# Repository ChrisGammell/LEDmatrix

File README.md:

# LEDmatrix
Simple LED Matrix board

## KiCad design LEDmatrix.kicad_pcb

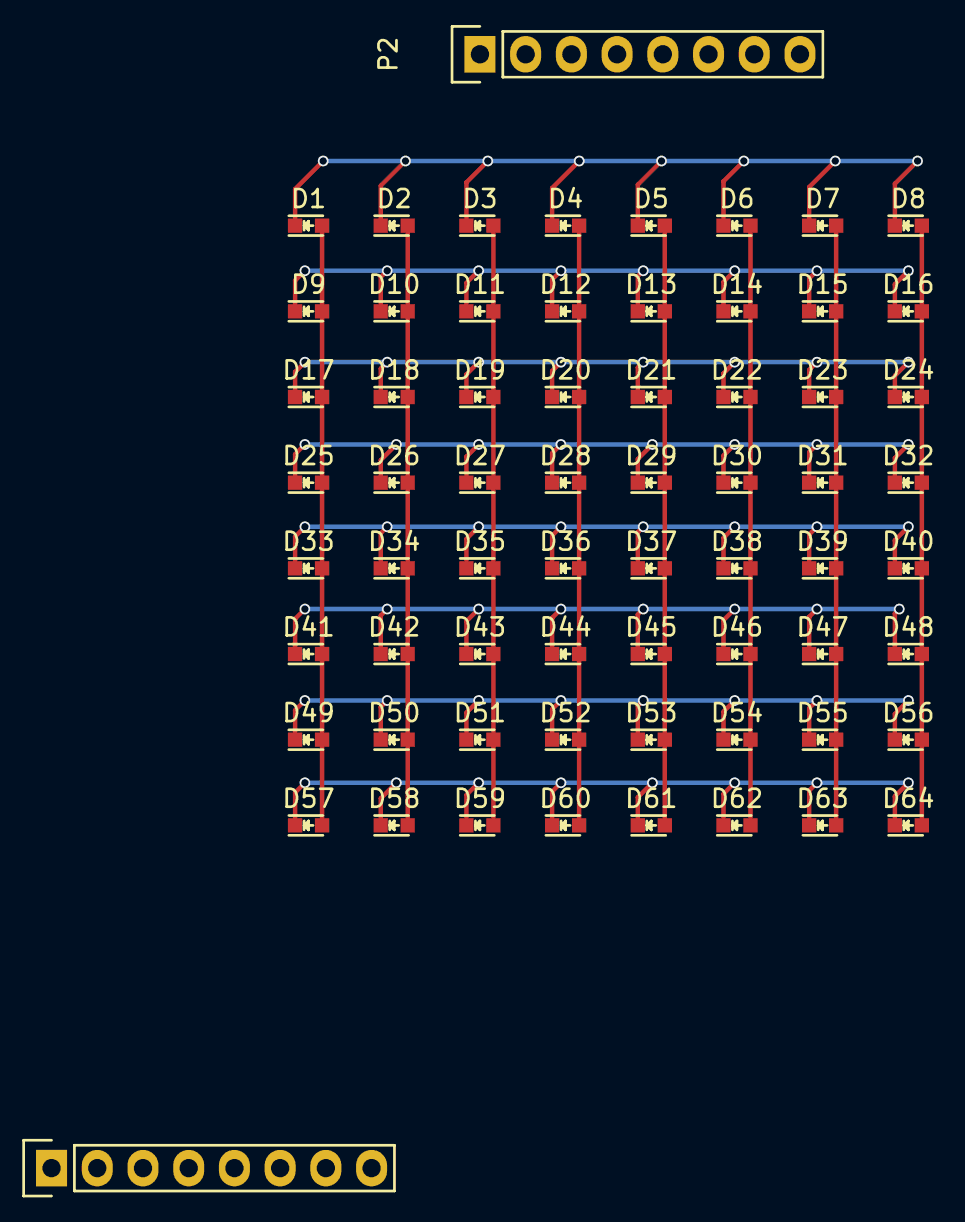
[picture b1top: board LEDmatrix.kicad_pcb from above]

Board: 2 copper layers, 66 parts (0 on the bottom side), 16 nets.

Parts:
D1, D2, D3, D4, D5, D6, D7, D8, D9, D10, D11, D12, D13, D14, D15, D16, D17, D18, D19, D20, D21, D22, D23, D24, D25, D26, D27, D28, D29, D30, D31, D32, D33, D34, D35, D36, D37, D38, D39, D40, D41, D42, D43, D44, D45, D46, D47, D48, D49, D50, D51, D52, D53, D54, D55, D56, D57, D58, D59, D60, D61, D62, D63, D64: LED; LED_0603
P1, P2: CONN_01X08; Pin_Header_Straight_1x08

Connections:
unnamed: D1.1, D2.1, D3.1, D4.1, D5.1, D6.1, D7.1, D8.1, P1.1
unnamed: D1.2, D9.2, D17.2, D25.2, D33.2, D41.2, D49.2, D57.2, P2.1
unnamed: D9.1, D10.1, D11.1, D12.1, D13.1, D14.1, D15.1, D16.1, P1.2
unnamed: D2.2, D10.2, D18.2, D26.2, D34.2, D42.2, D50.2, D58.2, P2.2
unnamed: D3.2, D11.2, D19.2, D27.2, D35.2, D43.2, D51.2, D59.2, P2.3
unnamed: D4.2, D12.2, D20.2, D28.2, D36.2, D44.2, D52.2, D60.2, P2.4
unnamed: D5.2, D13.2, D21.2, D29.2, D37.2, D45.2, D53.2, D61.2, P2.5
unnamed: D6.2, D14.2, D22.2, D30.2, D38.2, D46.2, D54.2, D62.2, P2.6
unnamed: D7.2, D15.2, D23.2, D31.2, D39.2, D47.2, D55.2, D63.2, P2.7
unnamed: D8.2, D16.2, D24.2, D32.2, D40.2, D48.2, D56.2, D64.2, P2.8
unnamed: D17.1, D18.1, D19.1, D20.1, D21.1, D22.1, D23.1, D24.1, P1.3
unnamed: D25.1, D26.1, D27.1, D28.1, D29.1, D30.1, D31.1, D32.1, P1.4
unnamed: D33.1, D34.1, D35.1, D36.1, D37.1, D38.1, D39.1, D40.1, P1.5
unnamed: D41.1, D42.1, D43.1, D44.1, D45.1, D46.1, D47.1, D48.1, P1.6
unnamed: D49.1, D50.1, D51.1, D52.1, D53.1, D54.1, D55.1, D56.1, P1.7
unnamed: D57.1, D58.1, D59.1, D60.1, D61.1, D62.1, D63.1, D64.1, P1.8

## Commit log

2016-03-04 Remove backup file
